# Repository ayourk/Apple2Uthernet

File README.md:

# Uthernet II

* The a2RetroSystems [Uthernet II](http://a2retrosystems.com/products.htm) product page
* The Uthernet II [User’s and Programmer’s Manual](http://dserver.macgui.com/Uthernet%20II%20manual%20draft.pdf)
* An Uthernet II [Applications Overview](http://www.a2retrosystems.com/downloads.htm)
* Some Uthernet II [Programming Infos](https://github.com/a2retrosystems/uthernet2/wiki)

## Description
Recreation of the Uthernet II Apple II Network Expansion Card using KiCAD 6.0.x.<br />
This version is a recreation of the Uthernet II board with the 80-pin WizNet W5100 chip.  
This version is NOT compatible with the [light pipe system](https://www.tindie.com/products/option8/uthernet-ii-light-pipe/) of the original.<br />
The cutout on the right is to accommodate [Adafruit's Panel Mount Ethernet Extension Cable](https://www.adafruit.com/product/909) if the card is put into Slot #2 on an Apple IIgs. <br />
Very little about the layout may need to be changed. <br />
Some parts may be difficult to source for PCB assembly unless you preorder them in advance.

### PCB Layout

### See Also
[Apple_II_Expansion Card_Specification](https://github.com/ayourk/Apple2Proto/raw/master/Apple_II_ExpansionCard_Spec.txt)

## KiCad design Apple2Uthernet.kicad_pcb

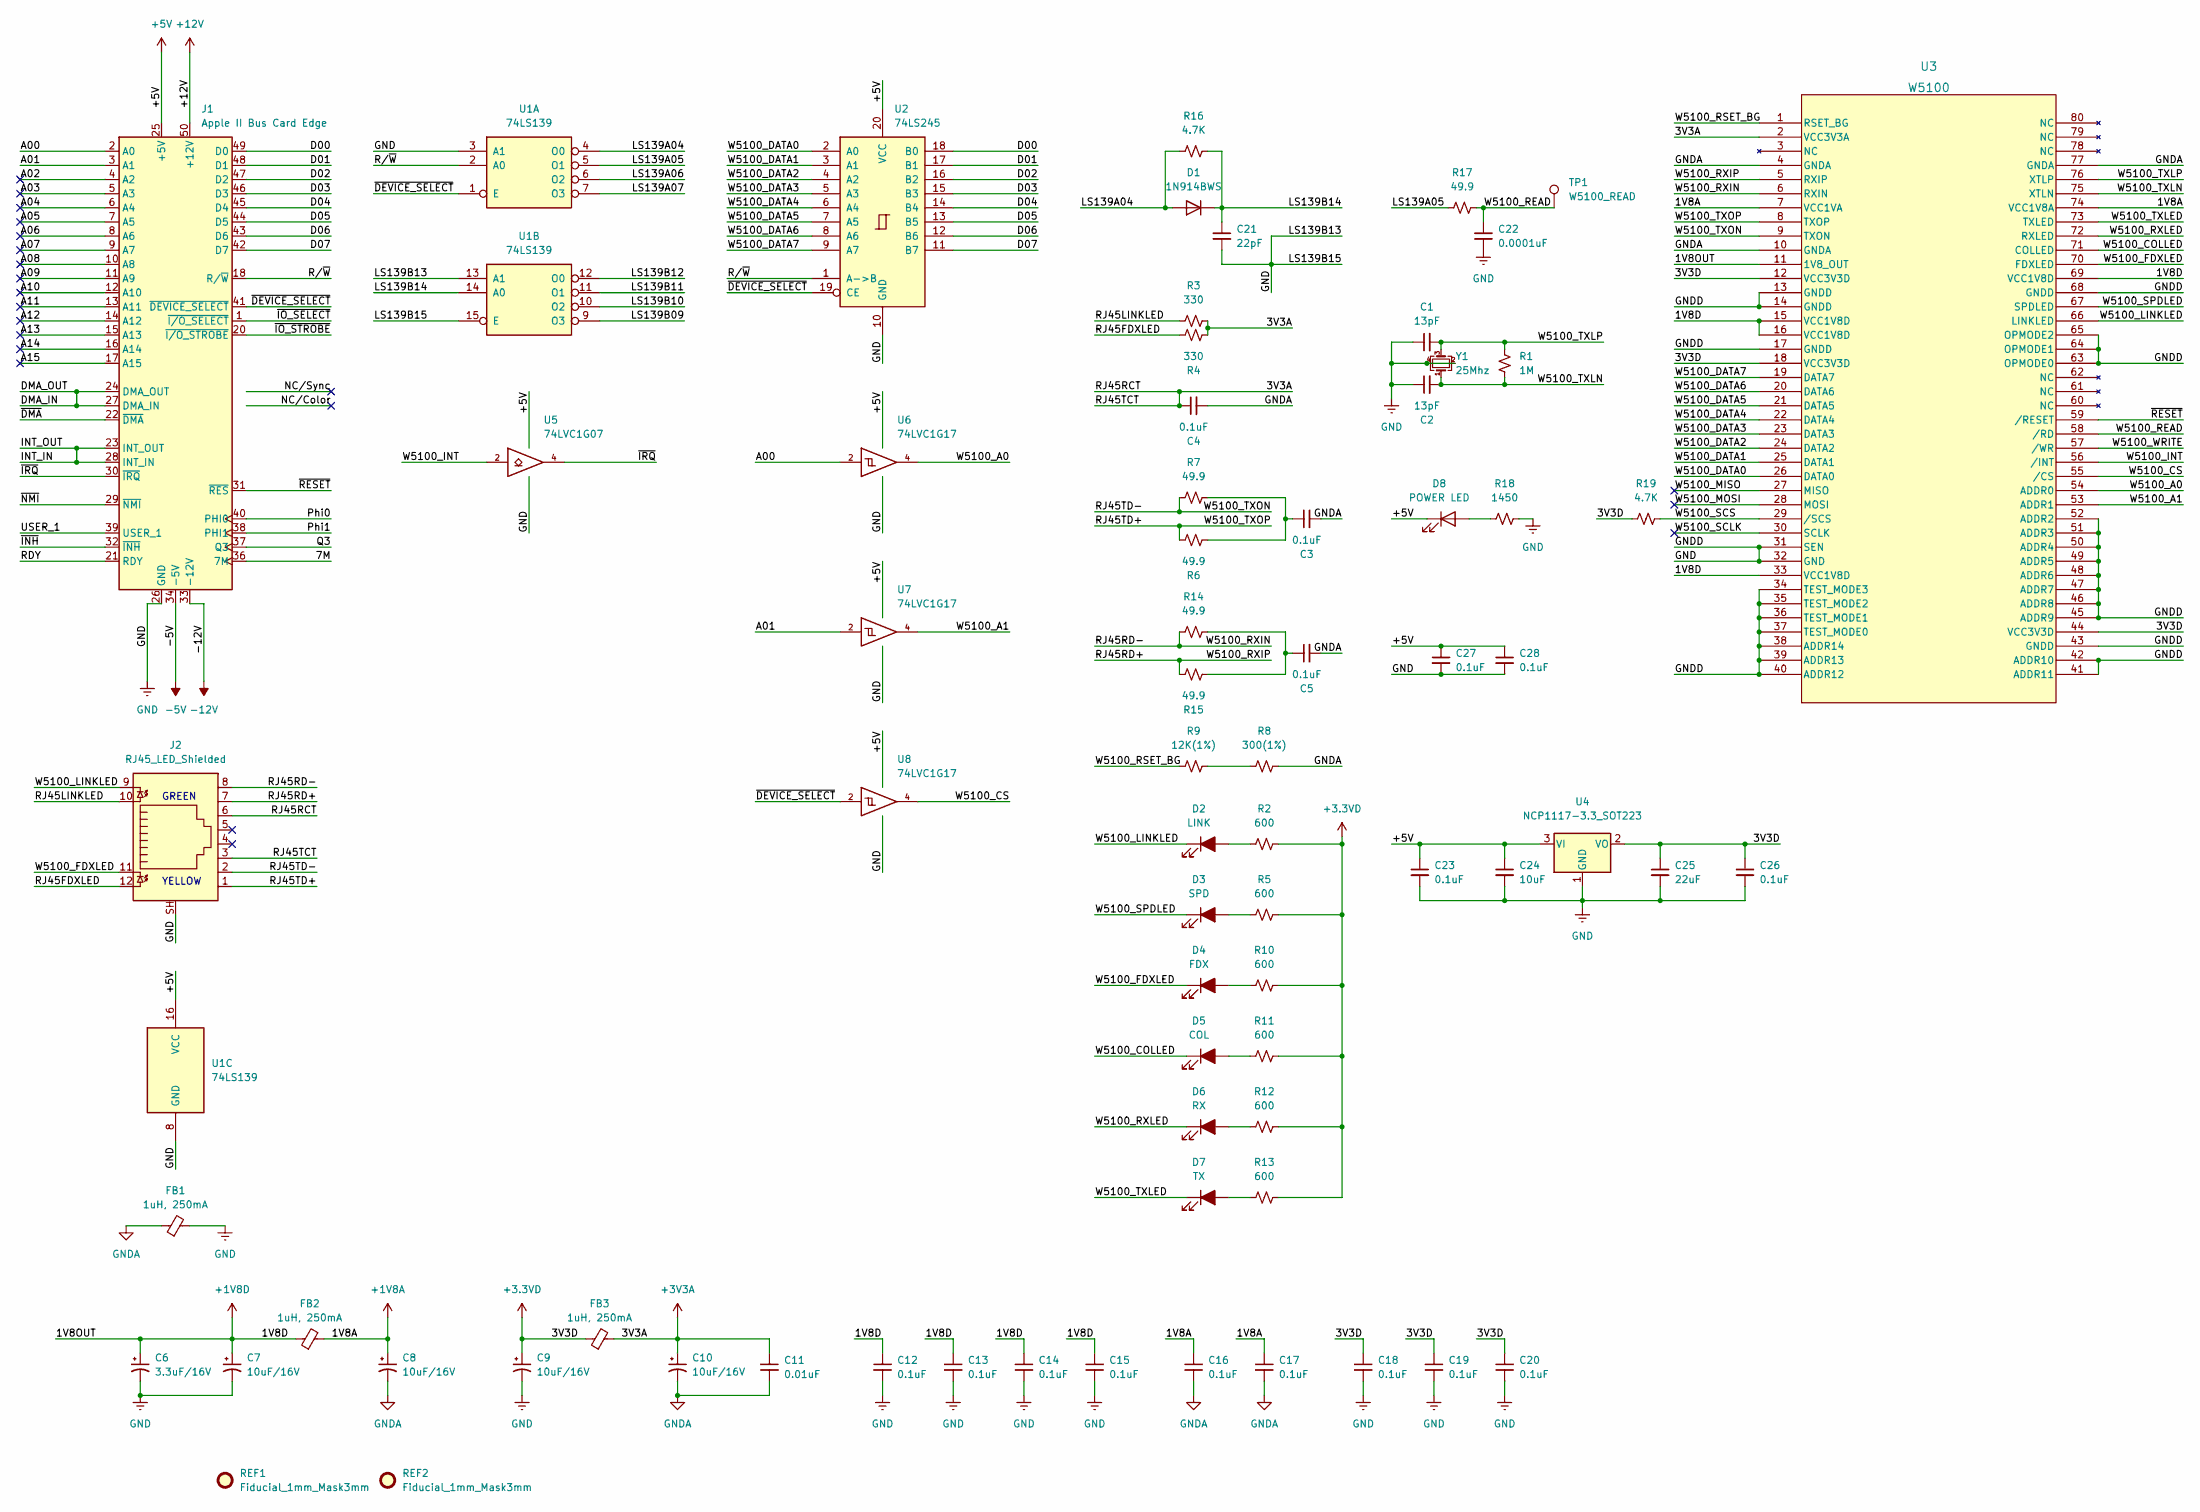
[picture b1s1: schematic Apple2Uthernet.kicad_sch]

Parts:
C1, C2: 13pF; C_0805_2012Metric_Pad1.18x1.45mm_HandSolder; MPN CC0805JRNPO9BN130; LCSC C519918
C3, C4, C5, C12, C13, C14, C15, C16, C17, C18, C19, C20, C23, C26, C27, C28: 0.1uF; C_0805_2012Metric_Pad1.18x1.45mm_HandSolder; MPN CL21B104KBCNNNC; LCSC C1711
C6: 3.3uF/16V; C_1206_3216Metric_Pad1.33x1.80mm_HandSolder; MPN T491A335M016AT; LCSC C1954959
C7, C8, C9, C10: 10uF/16V; C_1206_3216Metric_Pad1.33x1.80mm_HandSolder; MPN T494A106M016AT; LCSC C2798061
C11: 0.01uF; C_0805_2012Metric_Pad1.18x1.45mm_HandSolder; MPN CL21C103JBFNNNE; LCSC C27071
C21: 22pF; C_0805_2012Metric_Pad1.18x1.45mm_HandSolder; MPN CL21C220JB61PNC; LCSC C472837
C22: 0.0001uF; C_0805_2012Metric_Pad1.18x1.45mm_HandSolder; MPN CL21C101JBANNNC; LCSC C1790
C24: 10uF; C_0805_2012Metric_Pad1.18x1.45mm_HandSolder; MPN CL21B106KAYQNNE; LCSC C3039694
C25: 22uF; C_0805_2012Metric_Pad1.18x1.45mm_HandSolder; MPN CL21A226MAYNNNE; LCSC C602037
D1: 1N914BWS; D_SOD-523; MPN 1N914BWS; LCSC C2836064
D2: LINK; LED_0805_2012Metric_Pad1.15x1.40mm_HandSolder; MPN APT2012CGCK; LCSC C5875740
D3: SPD; LED_0805_2012Metric_Pad1.15x1.40mm_HandSolder; MPN APT2012CGCK; LCSC C5875740
D4: FDX; LED_0805_2012Metric_Pad1.15x1.40mm_HandSolder; MPN APT2012CGCK; LCSC C5875740
D5: COL; LED_0805_2012Metric_Pad1.15x1.40mm_HandSolder; MPN APT2012CGCK; LCSC C5875740
D6: RX; LED_0805_2012Metric_Pad1.15x1.40mm_HandSolder; MPN APT2012CGCK; LCSC C5875740
D7: TX; LED_0805_2012Metric_Pad1.15x1.40mm_HandSolder; MPN APT2012CGCK; LCSC C5875740
D8: POWER LED; LED_0805_2012Metric_Pad1.15x1.40mm_HandSolder; MPN APT2012CGCK; LCSC C5875740
FB1, FB2, FB3: 1uH, 250mA; L_0805_2012Metric_Pad1.15x1.40mm_HandSolder; MPN MLZ2012A1R0WT000; LCSC C88171
J1: Apple II Bus Card Edge; Bus_Apple_II_Card
J2: RJ45_LED_Shielded; RJ45-TH_XKB_X12ADAB1A3DY1027; MPN X12ADAB1A3DY1027; LCSC C2916459
R1: 1M; R_0805_2012Metric_Pad1.20x1.40mm_HandSolder; MPN ERJ-P06F1004V; LCSC C441997
R2, R5, R10, R11, R12, R13: 600; R_0805_2012Metric_Pad1.20x1.40mm_HandSolder; MPN ERJ-6ENF5900V; LCSC C2077453
R3, R4: 330; R_0805_2012Metric_Pad1.20x1.40mm_HandSolder; MPN ERJ-6ENF3300V; LCSC C410007
R6, R7, R14, R15, R17: 49.9; R_0805_2012Metric_Pad1.20x1.40mm_HandSolder; MPN CRCW080549R9FKEAHP; LCSC C204544
R8: 300(1%); R_0805_2012Metric_Pad1.20x1.40mm_HandSolder; MPN RC0805FR-07300RL; LCSC C114529
R9: 12K(1%); R_0805_2012Metric_Pad1.20x1.40mm_HandSolder; MPN RC0805FR-7W12KL; LCSC C408920
R16, R19: 4.7K; R_0805_2012Metric_Pad1.20x1.40mm_HandSolder; MPN ERJ-P06F4701V; LCSC C441984
R18: 1450; R_0805_2012Metric_Pad1.20x1.40mm_HandSolder; MPN ERJ-6ENF1431V; LCSC C336837
REF1, REF2: Fiducial_1mm_Mask3mm
TP1: W5100_READ
U1: 74LS139; SOP-16_3.9x9.9mm_P1.27mm; MPN XL74LS139; LCSC C521174
U2: 74LS245; SO-20_5.3x12.6mm_P1.27mm; MPN SN74LS245NSR; LCSC C7753
U3: W5100; 80LQFP_W5100_WIZ; MPN W5100; LCSC C18866
U4: NCP1117-3.3_SOT223; SOT-223-3_TabPin2; MPN NCP1117ST33T3G; LCSC C26537
U5: 74LVC1G07; SOT-23-5_HandSoldering; MPN SN74LVC1G07DBVR; LCSC C7829
U6, U7, U8: 74LVC1G17; SOT-23-5_HandSoldering; MPN SN74LVC1G17DBVR; LCSC C7836
Y1: 25Mhz; Crystal_SMD_5032-4Pin_5.0x3.2mm; MPN 405C35B25M00000; LCSC C252362

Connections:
+1V8: C6.1, C7.1, C12.1, C13.1, C14.1, C15.1, FB2.1, U3.11 (1V8_OUT), U3.15 (VCC1V8D), U3.16 (VCC1V8D), U3.33 (VCC1V8D), U3.69 (VCC1V8D)
+1V8A: C8.1, C16.1, C17.1, FB2.2, U3.7 (VCC1VA), U3.74 (VCC1V8A)
+3.3V: C9.1, C18.1, C19.1, C20.1, C25.1, C26.1, FB3.1, R2.2, R5.2, R10.2, R11.2, R12.2, R13.2, R19.1, U3.12 (VCC3V3D), U3.18 (VCC3V3D), U3.44 (VCC3V3D), U4.2 (VO)
+3V3A: C4.1, C10.1, C11.1, FB3.2, J2.3, J2.6, R3.2, R4.2, U3.2 (VCC3V3A)
+5V: C23.1, C24.1, C27.1, C28.1, D8.1 (K), J1.25 (+5V), U1.16 (VCC), U2.20 (VCC), U4.3 (VI), U5.5 (VCC), U6.5 (VCC), U7.5 (VCC), U8.5 (VCC)
+12V: J1.50 (+12V)
-5V: J1.34 (-5V)
-12V: J1.33 (-12V)
/7M: J1.36 (7M)
/A00: J1.2 (A0), U6.2
/A01: J1.3 (A1), U7.2
/A02: J1.4 (A2)
/A03: J1.5 (A3)
/A04: J1.6 (A4)
/A05: J1.7 (A5)
/A06: J1.8 (A6)
/A07: J1.9 (A7)
/A08: J1.10 (A8)
/A09: J1.11 (A9)
/A10: J1.12 (A10)
/A11: J1.13 (A11)
/A12: J1.14 (A12)
/A13: J1.15 (A13)
/A14: J1.16 (A14)
/A15: J1.17 (A15)
/D00: J1.49 (D0), U2.18 (B0)
/D01: J1.48 (D1), U2.17 (B1)
/D02: J1.47 (D2), U2.16 (B2)
/D03: J1.46 (D3), U2.15 (B3)
/D04: J1.45 (D4), U2.14 (B4)
/D05: J1.44 (D5), U2.13 (B5)
/D06: J1.43 (D6), U2.12 (B6)
/D07: J1.42 (D7), U2.11 (B7)
/DMA_IN: J1.24 (DMA_OUT), J1.27 (DMA_IN)
/INT_IN: J1.23 (INT_OUT), J1.28 (INT_IN)
/LS139A04: D1.2 (A), R16.1, U1.4 (O0)
/LS139A05: R17.1, U1.5 (O1)
/LS139A06: U1.6 (O2)
/LS139A07: U1.7 (O3)
/LS139B09: U1.9 (O3)
/LS139B10: U1.10 (O2)
/LS139B11: U1.11 (O1)
/LS139B12: U1.12 (O0)
/LS139B14: C21.1, D1.1 (K), R16.2, U1.14 (A0)
/NC/Color: J1.35 (NC/Color)
/NC/Sync: J1.19 (NC/Sync)
/Phi0: J1.40 (PHI0)
/Phi1: J1.38 (PHI1)
/Q3: J1.37 (Q3)
/RDY: J1.21 (RDY)
/RJ45FDXLED: J2.12, R4.1
/RJ45LINKLED: J2.10, R3.1
/RJ45RD+: J2.7, R15.1, U3.5 (RXIP)
/RJ45RD-: J2.8, R14.1, U3.6 (RXIN)
/RJ45TD+: J2.1, R6.1, U3.8 (TXOP)
/RJ45TD-: J2.2, R7.1, U3.9 (TXON)
/R/~W: J1.18 (R/~W), U1.2 (A0), U2.1 (A->B)
/USER_1: J1.39 (USER_1)
/W5100_A0: U3.54 (ADDR0), U6.4
/W5100_A1: U3.53 (ADDR1), U7.4
/W5100_COLLED: D5.1 (K), U3.71 (COLLED)
/W5100_CS: U3.55 (/CS), U8.4
/W5100_DATA0: U2.2 (A0), U3.26 (DATA0)
/W5100_DATA1: U2.3 (A1), U3.25 (DATA1)
/W5100_DATA2: U2.4 (A2), U3.24 (DATA2)
/W5100_DATA3: U2.5 (A3), U3.23 (DATA3)
/W5100_DATA4: U2.6 (A4), U3.22 (DATA4)
/W5100_DATA5: U2.7 (A5), U3.21 (DATA5)
/W5100_DATA6: U2.8 (A6), U3.20 (DATA6)
/W5100_DATA7: U2.9 (A7), U3.19 (DATA7)
/W5100_FDXLED: D4.1 (K), J2.11, U3.70 (FDXLED)
/W5100_INT: U3.56 (/INT), U5.2
/W5100_LINKLED: D2.1 (K), J2.9, U3.66 (LINKLED)
/W5100_MISO: U3.27 (MISO)
/W5100_MOSI: U3.28 (MOSI)
/W5100_READ: C22.1, R17.2, TP1.1, U3.58 (/RD)
/W5100_RSET_BG: R9.1, U3.1 (RSET_BG)
/W5100_RXLED: D6.1 (K), U3.72 (RXLED)
/W5100_SCLK: U3.30 (SCLK)
/W5100_SCS: R19.2, U3.29 (/SCS)
/W5100_SPDLED: D3.1 (K), U3.67 (SPDLED)
/W5100_TXLED: D7.1 (K), U3.73 (TXLED)
/W5100_TXLN: C2.2, R1.1, U3.75 (XTLN), Y1.1
/W5100_TXLP: C1.2, R1.2, U3.76 (XTLP), Y1.3
/W5100_WRITE: U3.57 (/WR)
/~DEVICE_SELECT: J1.41 (~DEVICE_SELECT), U1.1 (E), U2.19 (CE), U8.2
/~DMA: J1.22 (~DMA)
/~INH: J1.32 (~INH)
/~IO_SELECT: J1.1 (~I/O_SELECT)
/~IO_STROBE: J1.20 (~I/O_STROBE)
/~IRQ: J1.30 (~IRQ), U5.4
/~NMI: J1.29 (~NMI)
/~RESET: J1.31 (~RES), U3.59 (/RESET)
Earth: C1.1, C2.1, C6.2, C7.2, C9.2, C12.2, C13.2, C14.2, C15.2, C18.2, C19.2, C20.2, C21.2, C22.2, C23.2, C24.2, C25.2, C26.2, C27.2, C28.2, FB1.2, J1.26 (GND), J2.SH, R18.2, U1.3 (A1), U1.8 (GND), U1.13 (A1), U1.15 (E), U2.10 (GND), U3.13 (GNDD), U3.14 (GNDD), U3.17 (GNDD), U3.31 (SEN), U3.32 (GND), U3.34 (TEST_MODE3), U3.35 (TEST_MODE2), U3.36 (TEST_MODE1), U3.37 (TEST_MODE0), U3.38 (ADDR14), U3.39 (ADDR13), U3.40 (ADDR12), U3.41 (ADDR11), U3.42 (ADDR10), U3.43 (GNDD), U3.45 (ADDR9), U3.46 (ADDR8), U3.47 (ADDR7), U3.48 (ADDR6), U3.49 (ADDR5), U3.50 (ADDR4), U3.51 (ADDR3), U3.52 (ADDR2), U3.63 (OPMODE0), U3.64 (OPMODE1), U3.65 (OPMODE2), U3.68 (GNDD), U4.1 (GND), U5.3 (GND), U6.3 (GND), U7.3 (GND), U8.3 (GND), Y1.2, Y1.4
GNDA: C3.2, C4.2, C5.2, C8.2, C10.2, C11.2, C16.2, C17.2, FB1.1, R8.2, U3.4 (GNDA), U3.10 (GNDA), U3.77 (GNDA)
unnamed: C3.1, R6.2, R7.2
unnamed: C5.1, R14.2, R15.2
unnamed: D2.2 (A), R2.1
unnamed: D3.2 (A), R5.1
unnamed: D4.2 (A), R10.1
unnamed: D5.2 (A), R11.1
unnamed: D6.2 (A), R12.1
unnamed: D7.2 (A), R13.1
unnamed: D8.2 (A), R18.1
unnamed: R8.1, R9.2

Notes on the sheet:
GREEN
YELLOW

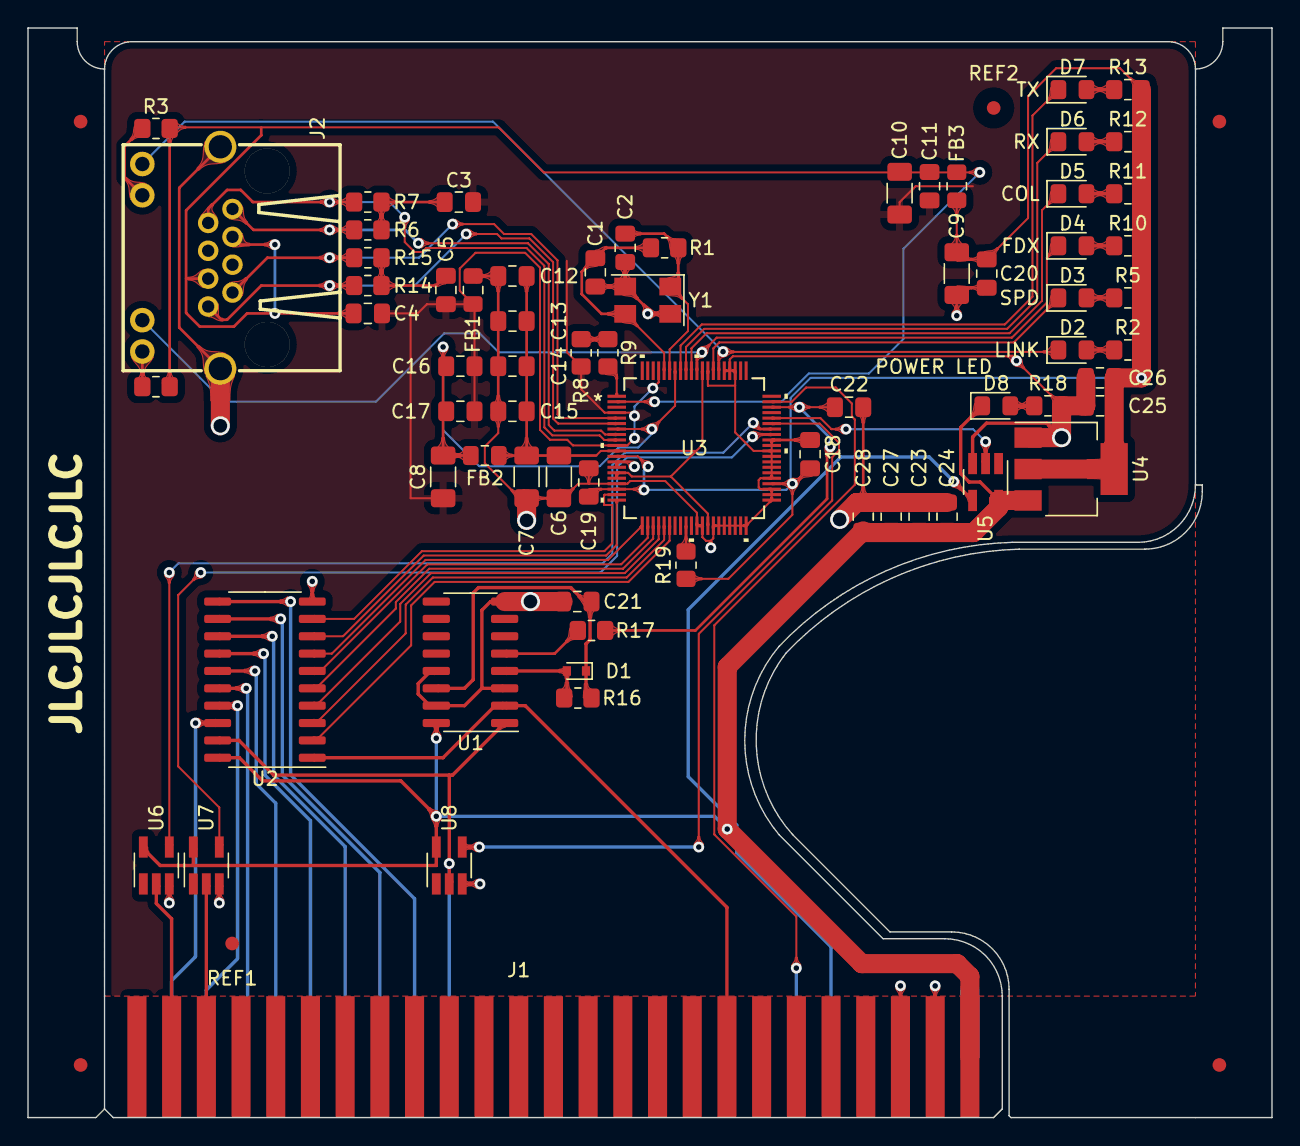
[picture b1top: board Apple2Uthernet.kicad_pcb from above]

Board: 2 copper layers, 91.0 x 79.7 mm, 71 parts (0 on the bottom side), 65 nets.

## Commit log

2024-04-07 Initial Commit of KiCAD 6.x files
2024-04-07 Update README.md
    Explained differences from original.
    Added picture of PCB layout.
2024-05-03 Updated PCB Layout to accomodate Adafruit Panel Mount Ethernet Extension Cable (PN 909). Made the board more compact. Updated project to render 3D models properly. Added edge rails/fiducials as per h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
2024-05-03 Update README.md
    Explained what the cut-out is for.
2024-05-03 Updated missing 3D model for clock crystal for render.
2024-05-14 Make the board taller so that fiducial rails go on the left and right sides.
2024-05-15 Added Fiducial Rails on the Left and Right sides.
2024-05-15 Updated Fiducial rails; Changed 1 resistor due to stocking issues.
